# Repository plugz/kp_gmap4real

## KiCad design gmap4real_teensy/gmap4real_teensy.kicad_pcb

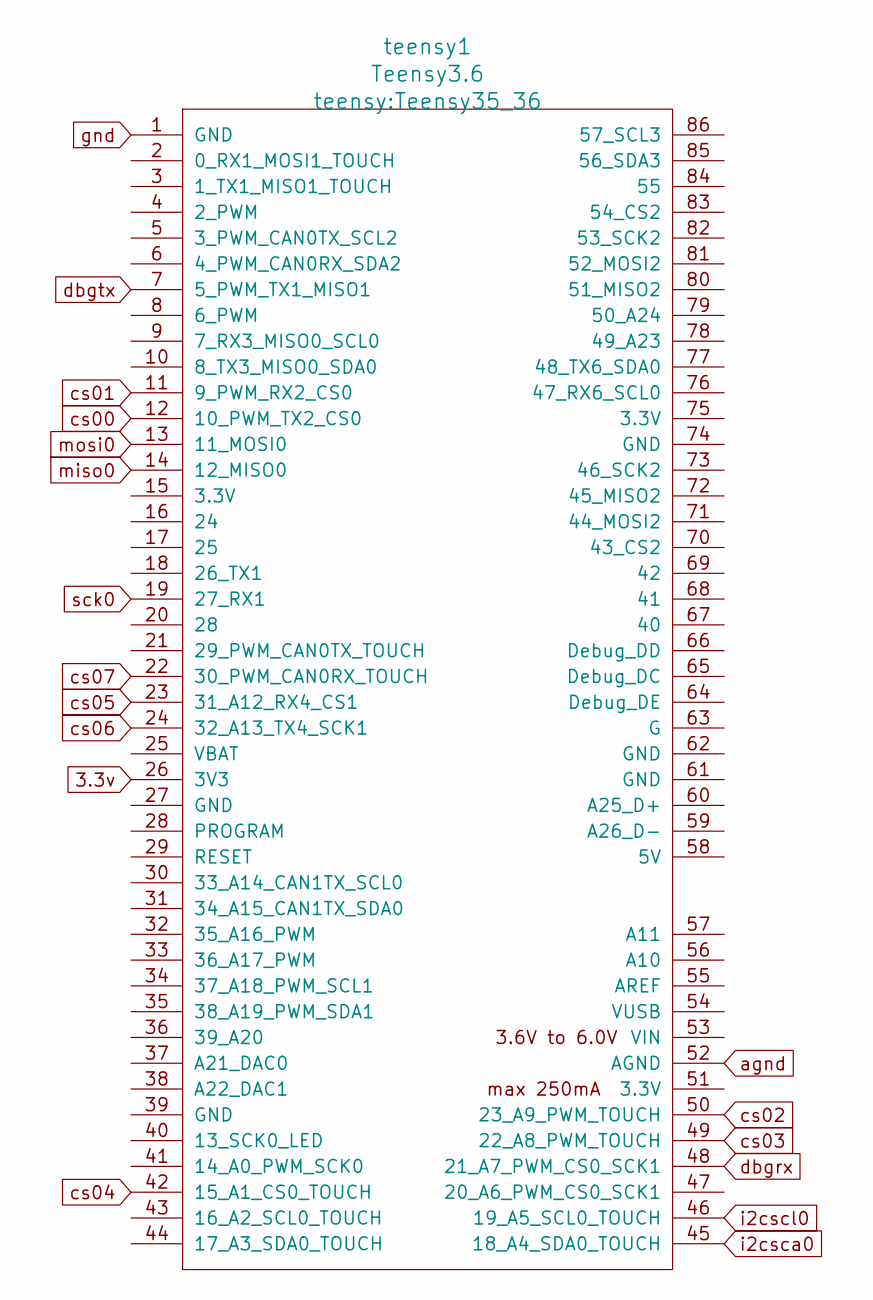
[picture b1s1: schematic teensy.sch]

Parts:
teensy1: Teensy3.6; Teensy35_36

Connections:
3.3v: teensy1.26 (3V3); also elsewhere on the board
agnd: teensy1.52 (AGND); also elsewhere on the board
cs00: teensy1.12 (10_PWM_TX2_CS0); also elsewhere on the board
cs01: teensy1.11 (9_PWM_RX2_CS0); also elsewhere on the board
cs02: teensy1.50 (23_A9_PWM_TOUCH); also elsewhere on the board
cs03: teensy1.49 (22_A8_PWM_TOUCH); also elsewhere on the board
cs04: teensy1.42 (15_A1_CS0_TOUCH); also elsewhere on the board
cs05: teensy1.23 (31_A12_RX4_CS1); also elsewhere on the board
cs06: teensy1.24 (32_A13_TX4_SCK1); also elsewhere on the board
cs07: teensy1.22 (30_PWM_CAN0RX_TOUCH); also elsewhere on the board
dbgrx: teensy1.48 (21_A7_PWM_CS0_SCK1); also elsewhere on the board
dbgtx: teensy1.7 (5_PWM_TX1_MISO1); also elsewhere on the board
gnd: teensy1.1 (GND); also elsewhere on the board
i2csca0: teensy1.45 (18_A4_SDA0_TOUCH)
i2cscl0: teensy1.46 (19_A5_SCL0_TOUCH); also elsewhere on the board
miso0: teensy1.14 (12_MISO0); also elsewhere on the board
mosi0: teensy1.13 (11_MOSI0); also elsewhere on the board
sck0: teensy1.19 (27_RX1); also elsewhere on the board

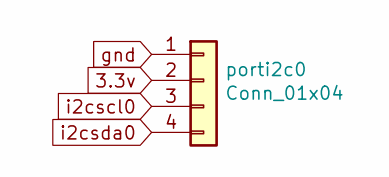
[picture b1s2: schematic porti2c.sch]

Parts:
porti2c0: Conn_01x04; PinHeader_1x04_P2.54mm_Vertical

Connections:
3.3v: porti2c0.2; also elsewhere on the board
gnd: porti2c0.1; also elsewhere on the board
i2cscl0: porti2c0.3; also elsewhere on the board
i2csda0: porti2c0.4

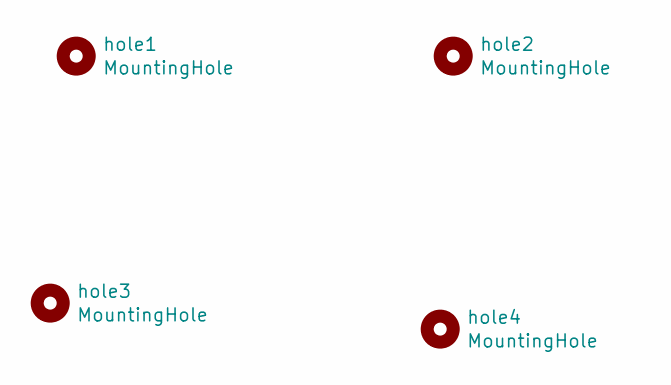
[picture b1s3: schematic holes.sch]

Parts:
hole1, hole2, hole3, hole4: MountingHole; MountingHole_3.2mm_M3_Pad

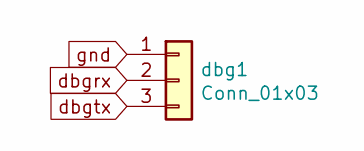
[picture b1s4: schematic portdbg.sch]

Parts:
dbg1: Conn_01x03; PinHeader_1x03_P2.54mm_Vertical

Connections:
dbgrx: dbg1.2; also elsewhere on the board
dbgtx: dbg1.3; also elsewhere on the board
gnd: dbg1.1; also elsewhere on the board

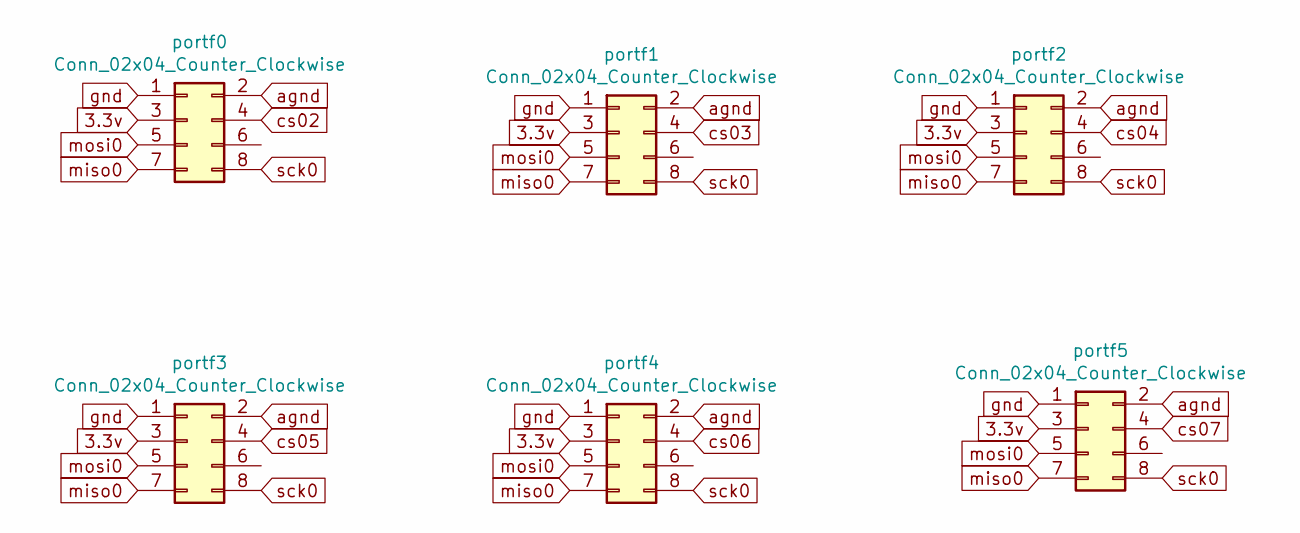
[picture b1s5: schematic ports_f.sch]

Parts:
portf0, portf1, portf2, portf3, portf4, portf5: Conn_02x04_Counter_Clockwise; IDC-Header_2x04_P2.54mm_Horizontal

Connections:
3.3v: portf0.3, portf1.3, portf2.3, portf3.3, portf4.3, portf5.3; also elsewhere on the board
agnd: portf0.2, portf1.2, portf2.2, portf3.2, portf4.2, portf5.2; also elsewhere on the board
cs02: portf0.4; also elsewhere on the board
cs03: portf1.4; also elsewhere on the board
cs04: portf2.4; also elsewhere on the board
cs05: portf3.4; also elsewhere on the board
cs06: portf4.4; also elsewhere on the board
cs07: portf5.4; also elsewhere on the board
gnd: portf0.1, portf1.1, portf2.1, portf3.1, portf4.1, portf5.1; also elsewhere on the board
miso0: portf0.7, portf1.7, portf2.7, portf3.7, portf4.7, portf5.7; also elsewhere on the board
mosi0: portf0.5, portf1.5, portf2.5, portf3.5, portf4.5, portf5.5; also elsewhere on the board
sck0: portf0.8, portf1.8, portf2.8, portf3.8, portf4.8, portf5.8; also elsewhere on the board

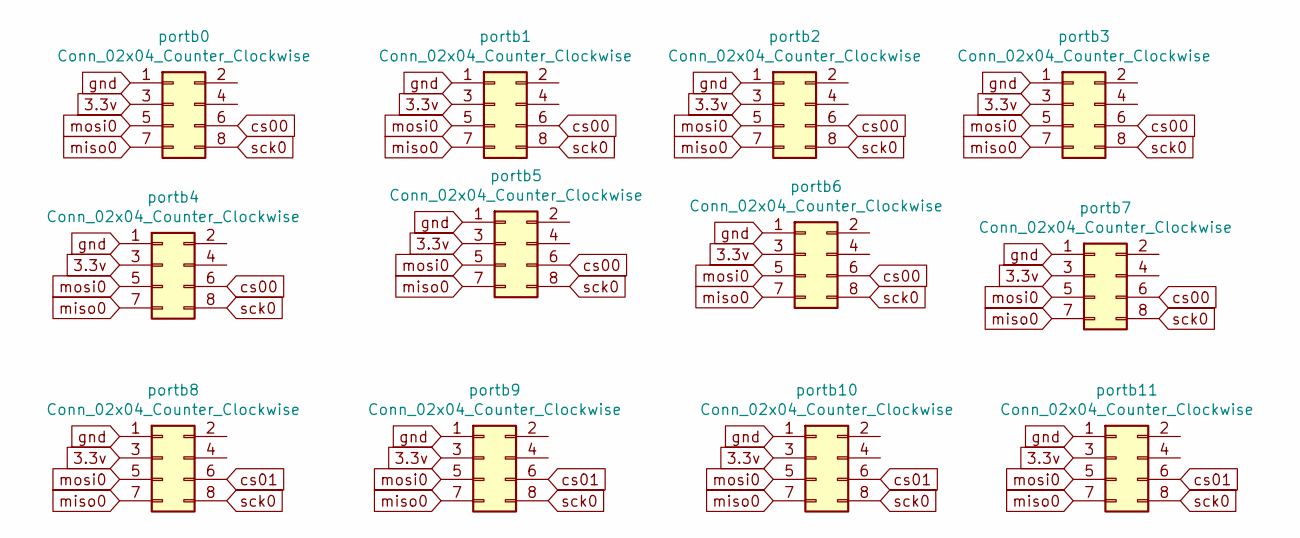
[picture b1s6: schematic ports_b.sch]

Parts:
portb0, portb1, portb2, portb3, portb4, portb5, portb6, portb7, portb8, portb9, portb10, portb11: Conn_02x04_Counter_Clockwise; IDC-Header_2x04_P2.54mm_Horizontal

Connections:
3.3v: portb0.3, portb1.3, portb2.3, portb3.3, portb4.3, portb5.3, portb6.3, portb7.3, portb8.3, portb9.3, portb10.3, portb11.3; also elsewhere on the board
cs00: portb0.6, portb1.6, portb2.6, portb3.6, portb4.6, portb5.6, portb6.6, portb7.6; also elsewhere on the board
cs01: portb8.6, portb9.6, portb10.6, portb11.6; also elsewhere on the board
gnd: portb0.1, portb1.1, portb2.1, portb3.1, portb4.1, portb5.1, portb6.1, portb7.1, portb8.1, portb9.1, portb10.1, portb11.1; also elsewhere on the board
miso0: portb0.7, portb1.7, portb2.7, portb3.7, portb4.7, portb5.7, portb6.7, portb7.7, portb8.7, portb9.7, portb10.7, portb11.7; also elsewhere on the board
mosi0: portb0.5, portb1.5, portb2.5, portb3.5, portb4.5, portb5.5, portb6.5, portb7.5, portb8.5, portb9.5, portb10.5, portb11.5; also elsewhere on the board
sck0: portb0.8, portb1.8, portb2.8, portb3.8, portb4.8, portb5.8, portb6.8, portb7.8, portb8.8, portb9.8, portb10.8, portb11.8; also elsewhere on the board

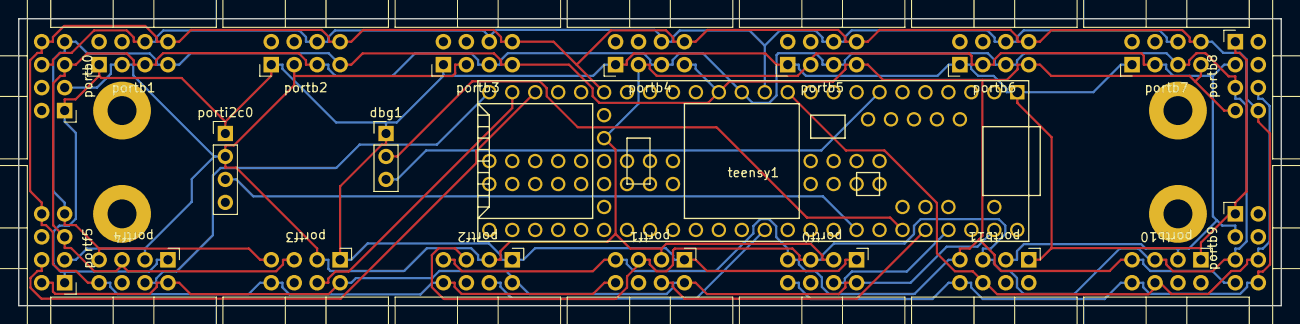
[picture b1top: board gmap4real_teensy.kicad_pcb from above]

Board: 2 copper layers, 139.7 x 31.8 mm, 25 parts (0 on the bottom side), 17 nets.

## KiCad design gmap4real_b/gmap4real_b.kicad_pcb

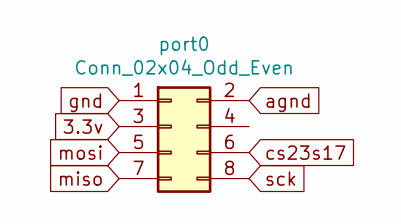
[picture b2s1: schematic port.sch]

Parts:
port0: Conn_02x04_Odd_Even; IDC-Header_2x04_P2.54mm_Horizontal

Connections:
3.3v: port0.3; also elsewhere on the board
agnd: port0.2
cs23s17: port0.6; also elsewhere on the board
gnd: port0.1; also elsewhere on the board
miso: port0.7; also elsewhere on the board
mosi: port0.5; also elsewhere on the board
sck: port0.8; also elsewhere on the board

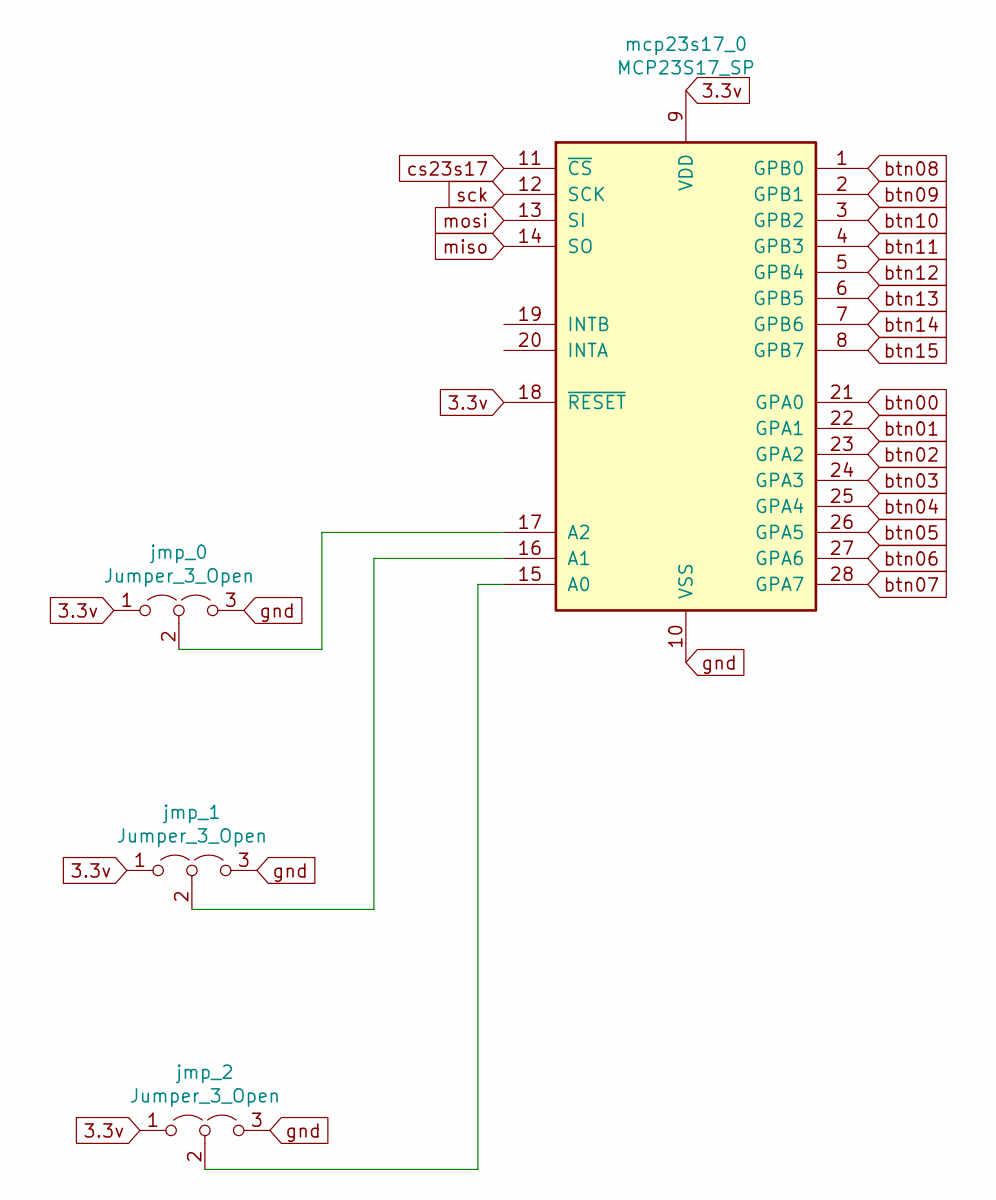
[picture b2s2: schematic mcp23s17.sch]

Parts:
jmp_0, jmp_1, jmp_2: Jumper_3_Open; PinHeader_1x03_P2.54mm_Vertical
mcp23s17_0: MCP23S17_SP; DIP-28_W7.62mm

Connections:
3.3v: jmp_0.1 (A), jmp_1.1 (A), jmp_2.1 (A), mcp23s17_0.9 (VDD), mcp23s17_0.18 (~RESET~); also elsewhere on the board
unnamed: jmp_0.2 (C), mcp23s17_0.17 (A2)
unnamed: jmp_1.2 (C), mcp23s17_0.16 (A1)
unnamed: jmp_2.2 (C), mcp23s17_0.15 (A0)
btn00: mcp23s17_0.21 (GPA0); also elsewhere on the board
btn01: mcp23s17_0.22 (GPA1); also elsewhere on the board
btn02: mcp23s17_0.23 (GPA2); also elsewhere on the board
btn03: mcp23s17_0.24 (GPA3); also elsewhere on the board
btn04: mcp23s17_0.25 (GPA4); also elsewhere on the board
btn05: mcp23s17_0.26 (GPA5); also elsewhere on the board
btn06: mcp23s17_0.27 (GPA6); also elsewhere on the board
btn07: mcp23s17_0.28 (GPA7); also elsewhere on the board
btn08: mcp23s17_0.1 (GPB0); also elsewhere on the board
btn09: mcp23s17_0.2 (GPB1); also elsewhere on the board
btn10: mcp23s17_0.3 (GPB2); also elsewhere on the board
btn11: mcp23s17_0.4 (GPB3); also elsewhere on the board
btn12: mcp23s17_0.5 (GPB4); also elsewhere on the board
btn13: mcp23s17_0.6 (GPB5); also elsewhere on the board
btn14: mcp23s17_0.7 (GPB6); also elsewhere on the board
btn15: mcp23s17_0.8 (GPB7); also elsewhere on the board
cs23s17: mcp23s17_0.11 (~CS~); also elsewhere on the board
gnd: jmp_0.3 (B), jmp_1.3 (B), jmp_2.3 (B), mcp23s17_0.10 (VSS); also elsewhere on the board
miso: mcp23s17_0.14 (SO); also elsewhere on the board
mosi: mcp23s17_0.13 (SI); also elsewhere on the board
sck: mcp23s17_0.12 (SCK); also elsewhere on the board

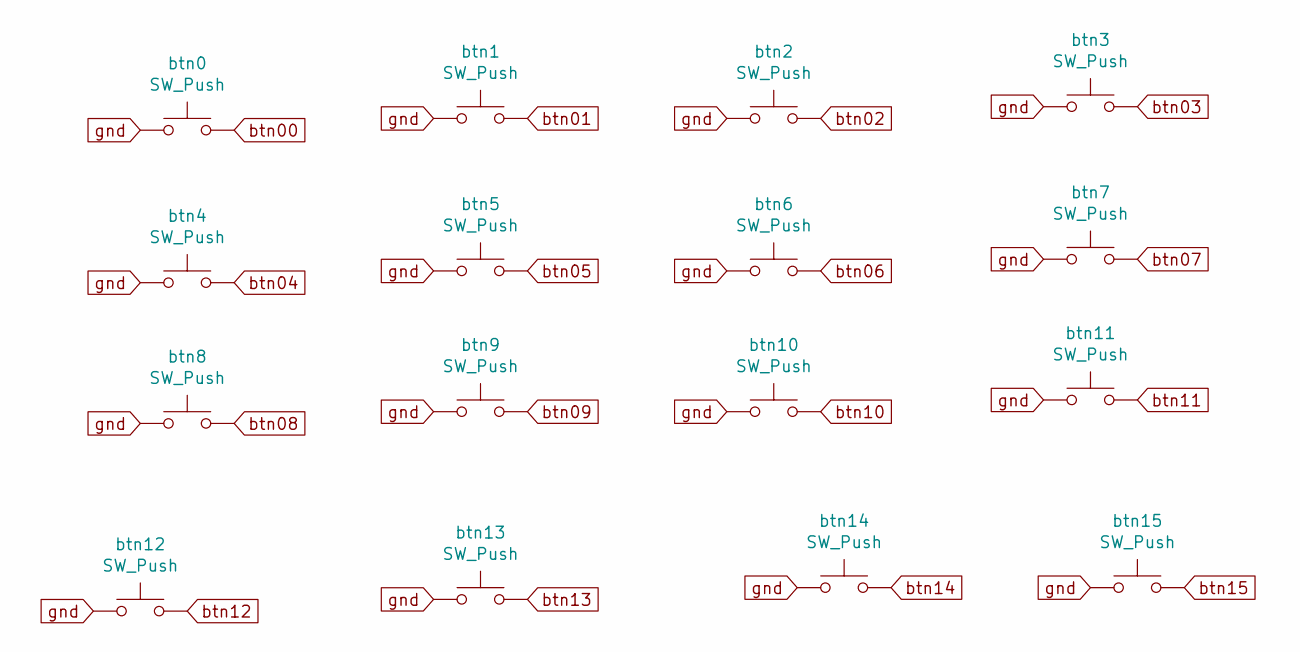
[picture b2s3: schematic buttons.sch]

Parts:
btn0, btn1, btn2, btn3, btn4, btn5, btn6, btn7, btn8, btn9, btn10, btn11, btn12, btn13, btn14, btn15: SW_Push; SW_Cherry_MX_1.00u_PCB_WITHLEDHOLE

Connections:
btn00: btn0.2; also elsewhere on the board
btn01: btn1.2; also elsewhere on the board
btn02: btn2.2; also elsewhere on the board
btn03: btn3.2; also elsewhere on the board
btn04: btn4.2; also elsewhere on the board
btn05: btn5.2; also elsewhere on the board
btn06: btn6.2; also elsewhere on the board
btn07: btn7.2; also elsewhere on the board
btn08: btn8.2; also elsewhere on the board
btn09: btn9.2; also elsewhere on the board
btn10: btn10.2; also elsewhere on the board
btn11: btn11.2; also elsewhere on the board
btn12: btn12.2; also elsewhere on the board
btn13: btn13.2; also elsewhere on the board
btn14: btn14.2; also elsewhere on the board
btn15: btn15.2; also elsewhere on the board
gnd: btn0.1, btn1.1, btn2.1, btn3.1, btn4.1, btn5.1, btn6.1, btn7.1, btn8.1, btn9.1, btn10.1, btn11.1, btn12.1, btn13.1, btn14.1, btn15.1; also elsewhere on the board

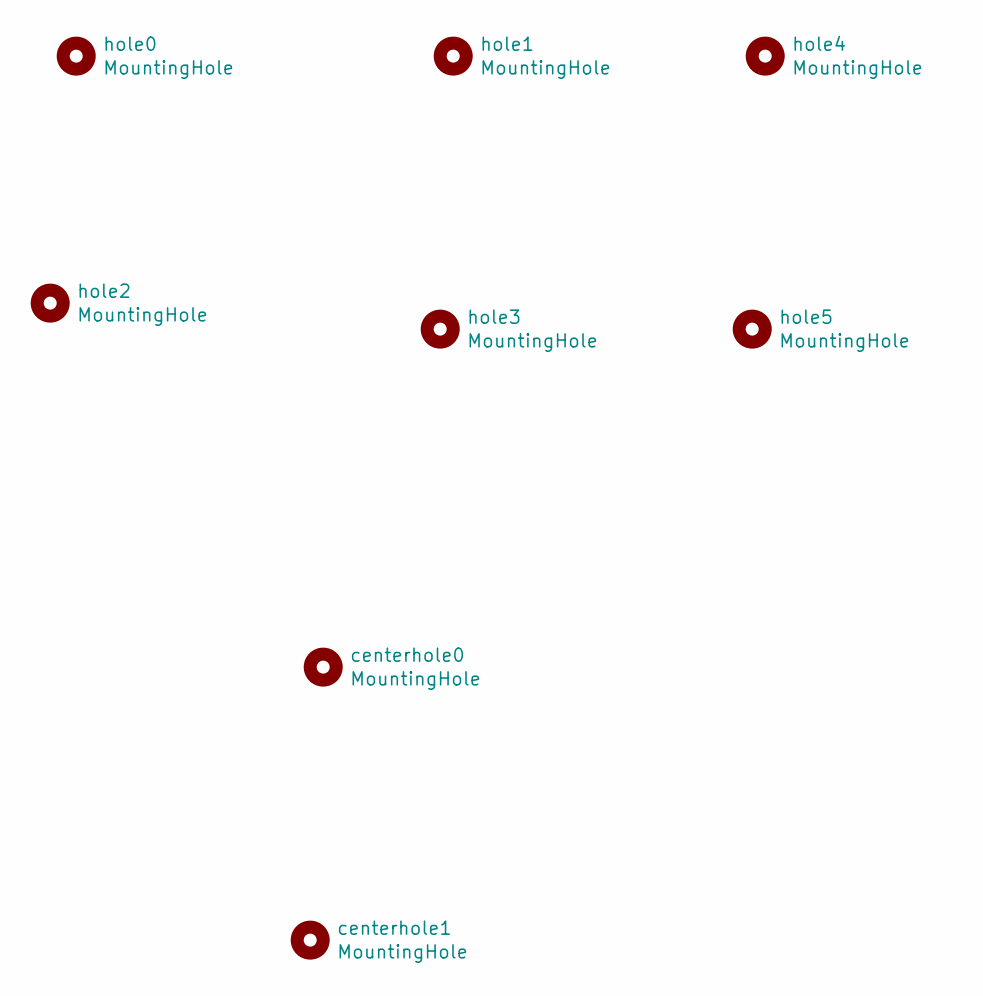
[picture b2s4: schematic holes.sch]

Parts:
centerhole0, centerhole1: MountingHole; MountingHole_3.2mm_M3_Pad
hole0, hole1, hole2, hole3, hole4, hole5: MountingHole; MountingHole_3.2mm_M3_Pad

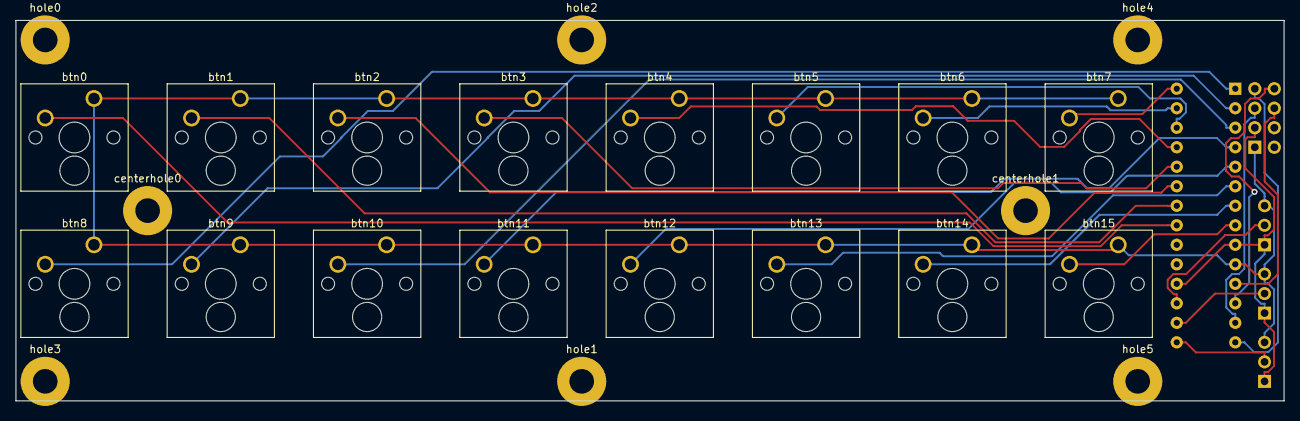
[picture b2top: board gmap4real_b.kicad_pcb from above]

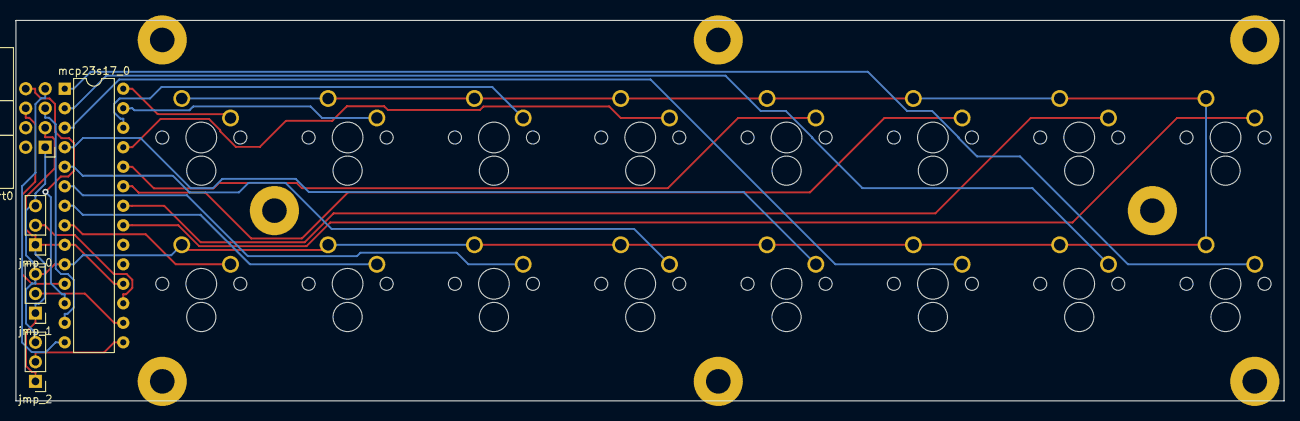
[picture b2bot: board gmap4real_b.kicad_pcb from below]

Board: 2 copper layers, 165.1 x 49.5 mm, 29 parts (5 on the bottom side), 25 nets.

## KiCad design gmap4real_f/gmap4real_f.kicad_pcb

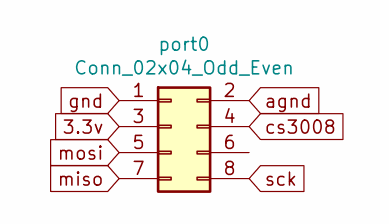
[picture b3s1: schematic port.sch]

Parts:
port0: Conn_02x04_Odd_Even; IDC-Header_2x04_P2.54mm_Horizontal

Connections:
3.3v: port0.3; also elsewhere on the board
agnd: port0.2; also elsewhere on the board
cs3008: port0.4; also elsewhere on the board
gnd: port0.1; also elsewhere on the board
miso: port0.7; also elsewhere on the board
mosi: port0.5; also elsewhere on the board
sck: port0.8; also elsewhere on the board

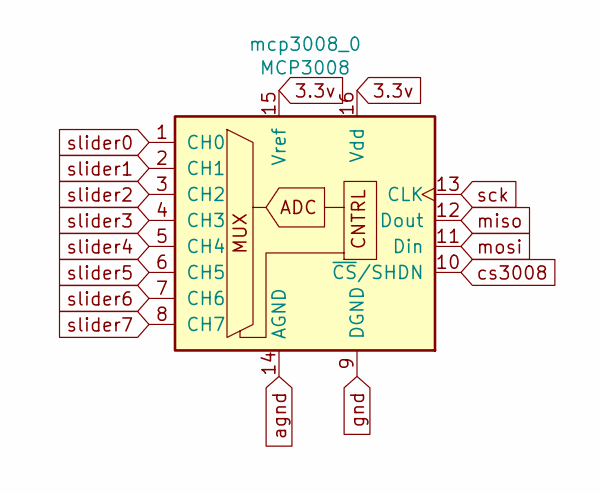
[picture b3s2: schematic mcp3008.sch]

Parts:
mcp3008_0: MCP3008; DIP-16_W7.62mm

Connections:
3.3v: mcp3008_0.15 (Vref), mcp3008_0.16 (Vdd); also elsewhere on the board
agnd: mcp3008_0.14 (AGND); also elsewhere on the board
cs3008: mcp3008_0.10 (~CS~/SHDN); also elsewhere on the board
gnd: mcp3008_0.9 (DGND); also elsewhere on the board
miso: mcp3008_0.12 (Dout); also elsewhere on the board
mosi: mcp3008_0.11 (Din); also elsewhere on the board
sck: mcp3008_0.13 (CLK); also elsewhere on the board
slider0: mcp3008_0.1 (CH0); also elsewhere on the board
slider1: mcp3008_0.2 (CH1); also elsewhere on the board
slider2: mcp3008_0.3 (CH2); also elsewhere on the board
slider3: mcp3008_0.4 (CH3); also elsewhere on the board
slider4: mcp3008_0.5 (CH4); also elsewhere on the board
slider5: mcp3008_0.6 (CH5); also elsewhere on the board
slider6: mcp3008_0.7 (CH6); also elsewhere on the board
slider7: mcp3008_0.8 (CH7); also elsewhere on the board

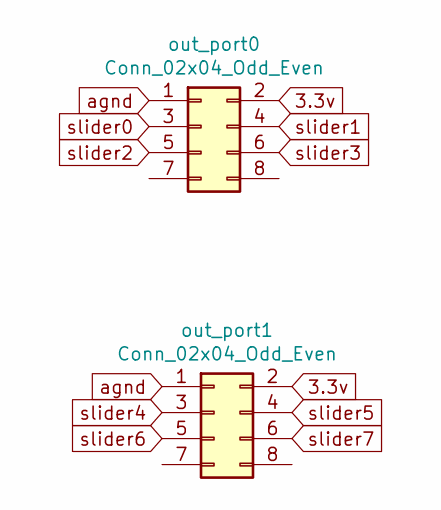
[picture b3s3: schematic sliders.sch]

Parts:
out_port0, out_port1: Conn_02x04_Odd_Even; IDC-Header_2x04_P2.54mm_Horizontal

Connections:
3.3v: out_port0.2, out_port1.2; also elsewhere on the board
agnd: out_port0.1, out_port1.1; also elsewhere on the board
slider0: out_port0.3; also elsewhere on the board
slider1: out_port0.4; also elsewhere on the board
slider2: out_port0.5; also elsewhere on the board
slider3: out_port0.6; also elsewhere on the board
slider4: out_port1.3; also elsewhere on the board
slider5: out_port1.4; also elsewhere on the board
slider6: out_port1.5; also elsewhere on the board
slider7: out_port1.6; also elsewhere on the board

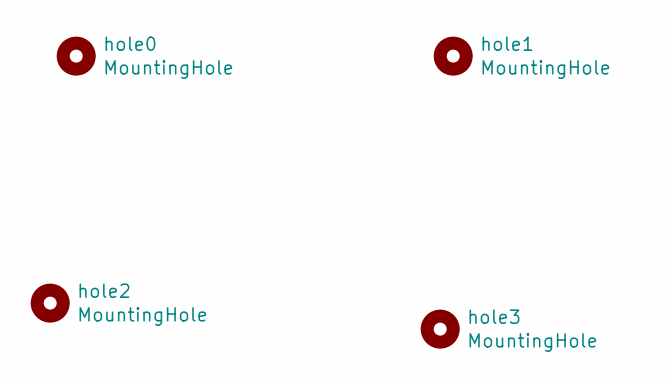
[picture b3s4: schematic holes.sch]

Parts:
hole0, hole1, hole2, hole3: MountingHole; MountingHole_3.2mm_M3_Pad

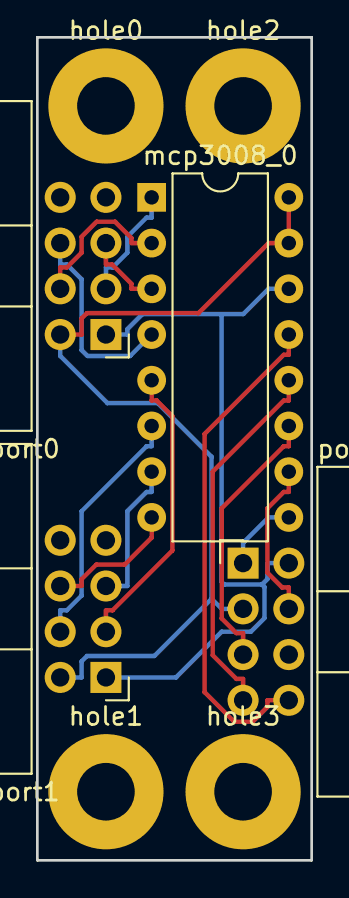
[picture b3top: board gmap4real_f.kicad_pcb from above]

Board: 2 copper layers, 15.2 x 45.7 mm, 8 parts (0 on the bottom side), 15 nets.

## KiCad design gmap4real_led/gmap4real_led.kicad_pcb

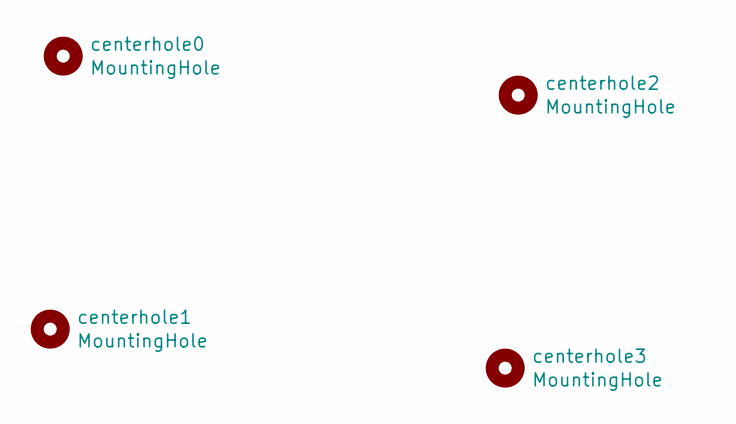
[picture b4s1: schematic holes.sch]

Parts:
centerhole0, centerhole1, centerhole2, centerhole3: MountingHole; MountingHole_3.2mm_M3_Pad

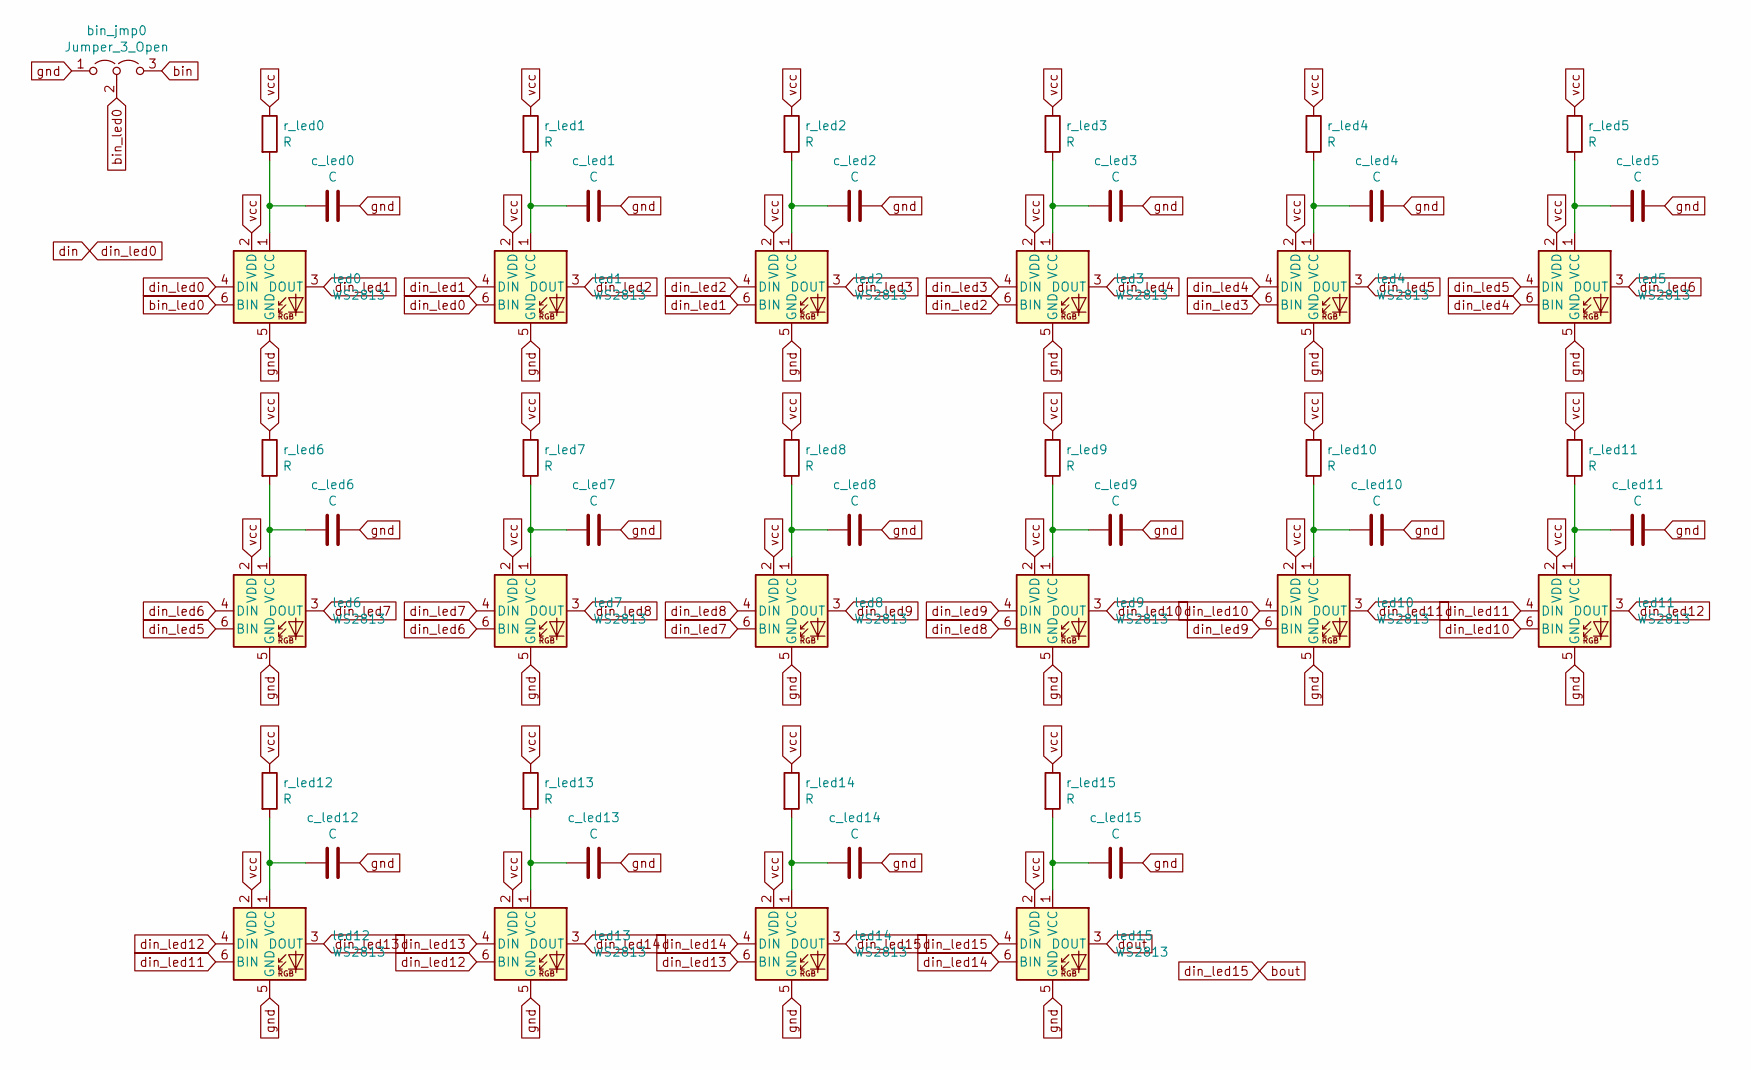
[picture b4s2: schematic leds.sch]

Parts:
bin_jmp0: Jumper_3_Open; PinHeader_1x03_P2.54mm_Vertical
c_led0, c_led1, c_led2, c_led3, c_led4, c_led5, c_led6, c_led7, c_led8, c_led9, c_led10, c_led11, c_led12, c_led13, c_led14, c_led15: C; C_0805_HandSoldering
led0, led1, led2, led3, led4, led5, led6, led7, led8, led9, led10, led11, led12, led13, led14, led15: WS2813; LED_WS2812-PLCC6
r_led0, r_led1, r_led2, r_led3, r_led4, r_led5, r_led6, r_led7, r_led8, r_led9, r_led10, r_led11, r_led12, r_led13, r_led14, r_led15: R; R_0402

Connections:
unnamed: c_led0.2, led0.1 (VCC), r_led0.2
unnamed: c_led1.2, led1.1 (VCC), r_led1.2
unnamed: c_led2.2, led2.1 (VCC), r_led2.2
unnamed: c_led3.2, led3.1 (VCC), r_led3.2
unnamed: c_led4.2, led4.1 (VCC), r_led4.2
unnamed: c_led5.2, led5.1 (VCC), r_led5.2
unnamed: c_led6.2, led6.1 (VCC), r_led6.2
unnamed: c_led7.2, led7.1 (VCC), r_led7.2
unnamed: c_led8.2, led8.1 (VCC), r_led8.2
unnamed: c_led9.2, led9.1 (VCC), r_led9.2
unnamed: c_led10.2, led10.1 (VCC), r_led10.2
unnamed: c_led11.2, led11.1 (VCC), r_led11.2
unnamed: c_led12.2, led12.1 (VCC), r_led12.2
unnamed: c_led13.2, led13.1 (VCC), r_led13.2
unnamed: c_led14.2, led14.1 (VCC), r_led14.2
unnamed: c_led15.2, led15.1 (VCC), r_led15.2
bin: bin_jmp0.3 (B); also elsewhere on the board
bin_led0: bin_jmp0.2 (C), led0.6 (BIN)
din_led0: led0.4 (DIN), led1.6 (BIN)
din_led1: led0.3 (DOUT), led1.4 (DIN), led2.6 (BIN)
din_led2: led1.3 (DOUT), led2.4 (DIN), led3.6 (BIN)
din_led3: led2.3 (DOUT), led3.4 (DIN), led4.6 (BIN)
din_led4: led3.3 (DOUT), led4.4 (DIN), led5.6 (BIN)
din_led5: led4.3 (DOUT), led5.4 (DIN), led6.6 (BIN)
din_led6: led5.3 (DOUT), led6.4 (DIN), led7.6 (BIN)
din_led7: led6.3 (DOUT), led7.4 (DIN), led8.6 (BIN)
din_led8: led7.3 (DOUT), led8.4 (DIN), led9.6 (BIN)
din_led9: led8.3 (DOUT), led9.4 (DIN), led10.6 (BIN)
din_led10: led9.3 (DOUT), led10.4 (DIN), led11.6 (BIN)
din_led11: led10.3 (DOUT), led11.4 (DIN), led12.6 (BIN)
din_led12: led11.3 (DOUT), led12.4 (DIN), led13.6 (BIN)
din_led13: led12.3 (DOUT), led13.4 (DIN), led14.6 (BIN)
din_led14: led13.3 (DOUT), led14.4 (DIN), led15.6 (BIN)
din_led15: led14.3 (DOUT), led15.4 (DIN)
dout: led15.3 (DOUT); also elsewhere on the board
gnd: bin_jmp0.1 (A), c_led0.1, c_led1.1, c_led2.1, c_led3.1, c_led4.1, c_led5.1, c_led6.1, c_led7.1, c_led8.1, c_led9.1, c_led10.1, c_led11.1, c_led12.1, c_led13.1, c_led14.1, c_led15.1, led0.5 (GND), led1.5 (GND), led2.5 (GND), led3.5 (GND), led4.5 (GND), led5.5 (GND), led6.5 (GND), led7.5 (GND), led8.5 (GND), led9.5 (GND), led10.5 (GND), led11.5 (GND), led12.5 (GND), led13.5 (GND), led14.5 (GND), led15.5 (GND); also elsewhere on the board
vcc: led0.2 (VDD), led1.2 (VDD), led2.2 (VDD), led3.2 (VDD), led4.2 (VDD), led5.2 (VDD), led6.2 (VDD), led7.2 (VDD), led8.2 (VDD), led9.2 (VDD), led10.2 (VDD), led11.2 (VDD), led12.2 (VDD), led13.2 (VDD), led14.2 (VDD), led15.2 (VDD), r_led0.1, r_led1.1, r_led2.1, r_led3.1, r_led4.1, r_led5.1, r_led6.1, r_led7.1, r_led8.1, r_led9.1, r_led10.1, r_led11.1, r_led12.1, r_led13.1, r_led14.1, r_led15.1; also elsewhere on the board
